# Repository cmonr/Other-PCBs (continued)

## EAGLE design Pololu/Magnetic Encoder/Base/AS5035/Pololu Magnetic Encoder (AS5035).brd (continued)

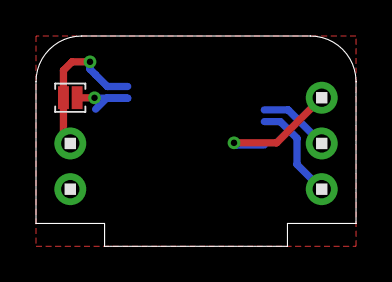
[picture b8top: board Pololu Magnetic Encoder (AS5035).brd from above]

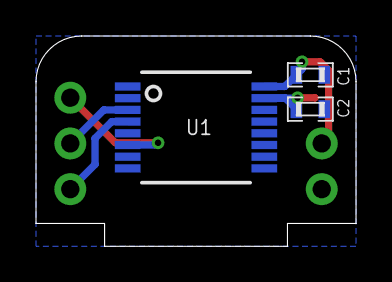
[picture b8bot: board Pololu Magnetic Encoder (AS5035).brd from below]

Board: 2 copper layers, 17.8 x 11.7 mm, 6 parts (3 on the bottom side), 6 nets.

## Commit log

2012-02-07 Massive initial commit.
2012-02-07 Github doesn't like the micro symbol...
2012-02-13 Created and completed USB to UART adapter based around MEC8 Edge Card connector part.
2012-02-13 Modified voltage connections to be next to each other. Easier to short.
2012-02-20 Changed connector to 2mm pitch as opposed to PCB connector
2012-02-20 A few minor tweaks
2012-07-25 Moved Pololu Magnetic Encoder files to v1 folder
2012-07-25 Created new version. Simplified circuit. Used right angle through hole headers.
2012-07-30 Not sure what changed to the Prototyping OTG Board...
2012-08-09 CHanged mounting hole part
2012-08-09 Created and completed schematic and PCB for MSP430 SMD programmer [QFN16]
2012-08-09 Renamed QFN to QFP
2013-01-24 Updated and renamed PCB Test to PCB Ruler
2013-01-24 Updated Pololu Magnetic Encoder, fixing pullup issue and adding new silkscreen info
2013-01-27 Updated website on silkscreen
2013-04-12 Created Robot Board ++ project.
2013-04-14 Added headers for 4 Motors, 4 Quad Enc, 6 ADCs, 6 Servos, Analog Line Sensor, 4 Mosfets, 4 GPIO. Added 2 Dual Mosfet ICs, IMU IC Remved WiFi IC, FTDI IC
2013-04-16 Finalized(?) board/headers layout Finalized LineSensor connector Connected ADC lines and Line Sensor to ADS7953
2013-04-18 Completed schematic of Vbatt -> 5v regulator Began board layout of Vbatt -> 5v regulator
    Considering bringing down max current supply from 8A to 6A (footprint for XAL1010 is large)
    Switched to 11-pin header for Line Sensor
    Created power select jumpters
    Named serial signals
    Added power supply signals
2013-04-20 Nearly completed Schematic layout Components on board are being arranged Upgraded to TPS53319 (14A w/ smaller Inductor) Need to find more IO for GPIO pins (consider using PCA9534 IO Expander) Most pa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
2013-04-23 Schematic tenatively completed. Changed Encoders to SPI (AS5050) Went down from 4 to 2 MOSFETs Went down from 16 to 6 IO Using 8 ADC to I2C converter for line sensor Pinouts finalized. Added indicato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
2013-04-23 Exported pictures of schematic and pcb in its current state
2013-04-25 Completed Schematic (tenatively...)
2013-04-25 Fixed Mosfet connections in Schematic Fixed 3.3v rail in Shcematic (3.3v meant to be decoupled between boards) Began routing signals on PCB
2013-04-25 Added board.png preview.
2013-04-25 Added 100uF capacitor to Servo Lines
2013-04-27 Routing fun! Redrawing ratsnest is now taking a measurable amount of time...
2013-04-27 Removed Line Sensor breakout. Replaced with I2C and UART breakout pins Will need to create an I2C to ADC breakout board sometime in the future...
    That line sensor connector was the worst...
2013-04-27 Added I2C and UART headers Connected most signals on PCB Will need to clean up...
2013-04-27 More routing. Most of the spaghetti wires taken care of. Need to fix widths....
2013-04-27 Ripped up all traces. Put as much on the top layer as possible
2013-04-29 most power lines routed
2013-04-29 More routing. Most motor control signals completed. Successfully making larger ground plane.
2013-04-29 More routing. Everything below the switching regulators completed!
2013-04-29 No airwires left!!! ^_^
    Time for a nap...
2013-04-29 Routing complete!
    Lol, nap.
2013-05-01 Removed SMD jumpers for Motors. Will put onto adapter instead. Layout and silkscreen on board tenatively completed. Schematic will be cleaned up after Senior design paper due tomorrow.
2013-05-01 Modified Schematic. Will need to be cleaned up. Added two ICs to look into (SPI Stereo DAC & Audio Amp)
2013-05-02 Removed ICs for Audio in list of ToDo Minorly adjusted bottom silk screen
    Barring any major issues, board will be sent out to be manufactured tomorrow!
2013-05-02 Removed silkscreen from launchpas part; didn't like it.
2013-05-02 Organizing folders into subdirectories for upcoming projects
2013-05-03 Renamed files. Corrected uSD Card package. All other ICs check out.
2013-05-03 Some more file management w/ the Pololu Encoders
2013-05-03 More file management. Created new project for AS5050 Serial Magnetic Encoder
2013-05-03 Created and completed AS5050 Encoder PCB
2013-05-03 REmoved bDocu sik screen mistakes
2013-05-04 Created BeagleBone Arduino Cape project Using premade outlines to figure out which pins to use for UART
2013-05-07 Created and completed tiny I2C to ADC Adapter
2013-05-08 Began working on Dual Motor Adapter for Robotics Booster Pack.
    Shelving project until after Finals & once Robotics Booster Pack is verified to be fully functional.
2013-05-27 Modified Silkscreen and placement of hole.
2013-07-24 Cleaned up I2C Line Sensor. Added 5 ohm resistor as per datasheet. Updated footprints and removed Zero Force Connector.
2013-07-24 Added images for I2C Line Sensor
2013-07-24 Fixed silk screen error...
2013-07-24 Created I2C Mini Line Sensor
2013-07-24 Added address select pins for IC
2013-08-01 Creating base board for Pololu Black Motor Mount
2013-08-01 Messing with encoders. Created base plate for Black Mount Created two PCBs for base-less/floating encoder
2013-08-01 Removed extra files
2013-08-01 Renamed files
2013-08-01 Removing more extra files...
2013-08-03 Added via on both Base plates for OSHPark submission
2013-08-08 Cleaned up layout of I2C Mini Line Sensor and I2C Line Sensor Also geenerated preview images
2013-08-08 Generated updated images for Robotics Booster Pack
2013-08-10 Added decoupling capacitor to motor connetions Made 'oval' vias for motors
    All in all, should now fit motors
2013-08-11 Addressed all issues in github repo Moved GPIO & Mosfet connections up because of USB connector in Launchpad Fixed SPI pin swap Added diode between 5v and VBUS Changed jumpers for UART BT/XBee select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
2013-08-13 Created AS5035 FLoating Encoder
2013-08-13 Modified CAM setting to manufacture correctly
2013-08-13 Changed Pinouts of BoosterPack * SPI Encoders replaced with QEI * SD Card/SPI interface moved to port F * Motor Control Signals moved to port A
    Layout still needs to be redone...
2013-08-15 Cleaned up AS5035 based Magnetic Encoder. Added Silkscreen adn removed SPI components.
2013-08-15 Added C1 & C2 on bottom silkscreen
2013-08-17 CS should be tied low for QEI to work on the AS5035
2013-08-17 Updated board and schematic previews
2013-08-25 Added old Binary Clock project
2013-08-25 Generated images for PCB Ruler
2013-08-25 Regenerate screnshots
2013-08-26 Removed projects that I'm unlikely to ever get to again.
2013-08-26 Minor Updates to I2CLine Sensor Removed header labeling on bottom layer and spaced resistors away from IR sensors
2013-08-26 Added drill holes in slot
2013-08-26 Fixed Silkscreen issues
2013-08-26 Updated Board Preview
2013-08-26 Cleaned up files
2013-09-03 Changd R[1-4] values to 51 ohms instead of 33 ohms. PCBs should no longer heat up due to current draw.
2013-09-10 Started routing v2. And by started, I mean rerouting _everything_
    ... The heck's wrong with me ...
2013-09-10 Modified resistor values such that the PCBs should no longer get hot
2013-09-15 Making progress on PCB re-layout. Moved some pins around to make routing _much_ easier, along with the added improvements.
2013-10-06 Replaced 5v regulator circuit with TPS5450 Added more power options in the form of SMD Jumpers Added IO Expander-controlled Servo FET Swapped positions of XBee and extra IO/FETs to make routing simpl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
2013-10-07 Added F387 Trinket
2013-10-07 Added Fume Extractor
2013-10-24 Modifed Robotics BP regulators, along with a few other things
2013-10-25 Cleaned up Servo.EN connections and indicator LEDs Routing will soon begin. It's unreasonable to believe that it will all be complete by the end of the weekend, bu some goals aren't meant to be met.
2013-10-26 Began routing of Robotics BP v2 Bluetooth, XBee, and UART mux routing nearly complete. Started LEDs and IMU routing.
2013-11-04 More Robotics BP v2 routing. Power regulators routed and completed Most IO Expander signals completely routed
2013-11-05 More Routing for Robotics Booster Pack v2. Assuming UART0 header is oriented correctly, the top 25% of board is completely routed!
2013-11-07 Even more routing! With any luck, all routing will be completed by the end of tomorrow ^^;
2013-11-08 Robotics BoosterPack v2 Complete! Still need to double check a few mote things, and clean up the silkscreen.
2013-11-08 Cleaned up completed Robotics Booster Pack v2. Sent off to OSHPark!
2013-11-12 Redid Trinket clone to add FTDI header capabilities Replaced USB ESD protection IC with tinier variant. All passives are now 0402 sized (oh boy...) Power domains should be fixed as well
2013-11-13 Completed uDev C8051 PCB (tiny as FUCK) Renamed files from F287 Trinket to uDev C8051
2013-11-27 Cleaned up part names
2014-04-12 Began starting on v2.1 Removed: Bluetooth Module, Servo Enable IC, Buffer IC. Corrected Motor PWM/IO signals issue Centered power ICs
2014-05-07 Let the carnage that shall be known as v3 begin!
2014-05-08 Continued working on RBP v3 Using TPS62177 for 3.3v regulator circuit, new Vin headers, moving things around.
2014-05-09 COntinuing work on RBP v3 Added smd headers to replace Launchpad throguh hole headers (more routing space on the bottom) Moved around motor controllers -n- stuff.
2014-05-10 Continuing RBP v3 rerouting. Figured out desired placement of headers. Thinking of adding FET to control power going out of board (NTMFS4897NFT1G). Need to replace IO expander; might need 16 pins ins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
2014-05-11 Got everything mostly figured out as to where I want things. Using larger capacitors. Pin header mappings decided on. Routing will be hell... Still need to figure out how to distribute all power vari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
2014-05-11 Part placement ~90% completed. Started routing. Pin mapping figured out (for the most part).
2014-05-11 Updated images.
2014-05-11 Part placement is mostly complete for RBP v3. Layout coming along. Routing multiple Power Header Options will be difficult...
2014-05-12 More routing. Completed Motor Controller power traces and 3.3v & 5v regulator power traces.
2014-05-14 More routing fun! Got a significant amount ofpower signals rounted. Replaced 1W 1mOhm power resistor with 3W 0.5mOhm resistor (able to carry much more current)
2014-05-17 Board completely routed! Silkscreen needed, and final mulling/triple check needed, but otherwise, it's nearly ready to be made!
2014-05-17 Robitcs BPv3 cleaned up, with silkscreen added. Ready to be fabricated!
